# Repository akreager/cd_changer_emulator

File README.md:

# CD Changer Emulator

**Raspberry Pi-based CD changer emulator for vintage Kenwood car stereos**

Reverse-engineering the proprietary serial protocol used by 1990s Kenwood head units to communicate with their CD changers, and building an open-source emulator that replaces the changer with a Raspberry Pi — enabling unlimited music playback through the original stereo using its factory controls.

## Project Status

🔬 **Phase: Protocol Reverse Engineering** — Capturing and decoding the synchronous serial protocol between a Kenwood KRC-3006 cassette receiver and a KDC-C717 10-disc CD changer.

### Current Milestone

**Phase 1 of TP-KRC3006-01 — power-on characterization — was executed; closeout is pending.** Executed 2026-04-19 on the KRC-3006 with a KDC-C717 changer connected through the pass-through breakout board. The overall result, continuity P/F and several dispositions remain blank (DC-02); results are published in [TL-KRC3006-01-P1-20260419](./docs/records/TL-KRC3006-01-P1-20260419.pdf).

Findings that matter for the emulator design:

- **CH-CON (Pin 4) measures active-HIGH** — the line rises when the changer source is selected. This *conflicts* with the KDC-CX85 service manual, which documents it as active-LOW. To be re-confirmed against decoded traffic in Phase 2.
- **Pin 2 (GND) and Pin 6 (D.GND) show continuity** inside the head unit, which settles the grounding strategy for the HAT.
- **CLK (Pin 13) is gated, not continuous** — 0 Hz at idle, 31.6 Hz during playback, briefly ~100 Hz on a track change before settling back. These are DMM frequency readings on a gated line, not bit-rate measurements; bit-level clock timing awaits logic analyzer capture in Phase 2A.
- **Pin 10 (CH-DATAC) idles near 5 V**, not the LOW state predicted by the schematic analysis. Unexplained — still open.
- **The KDC-C717 is functional** — displays E-01 with no magazine, then loads and plays on insertion.

Testing runs inline through the DN-KRC3006-04 pass-through breakout board, serial number 1, assembled and verified per TP-KRC3006-02:

The KDC-CX85 originally used as the reference changer was diagnosed with a dead or degraded laser diode and retired. All further testing uses the KDC-C717:

For reference, the 13-pin mini DIN changer connector pinout:

### Immediate To-Do

- [ ] **Close out Phase 1** — Complete the missing results, deviations and changer-present observation in the separate supplement required by [D-1](.agents/decisions.md). The original [Phase 1 record](docs/records/TL-KRC3006-01-P1-20260419.pdf) stays unchanged; Phase 2A requires its overall disposition (DC-02/03).
- [ ] **Execute Phase 2A** — With the C717 connected and no magazine, capture the A/B/C power/source transitions, measure timing and decode a repeatable frame using [TP-01 §4.2](docs/TP-KRC3006-01.md#42-phase-2a-idle-capture-changer-connected-no-magazine) and the matching TL-01 tab. The head unit needs a changer present to select CD-CH; the supplement will record the date and setup of that owner observation.
- [ ] **Build and verify FIX-01 in parallel** — Modify breakout S/N 2 under [DN-04 §16](docs/DN-KRC3006-04.md#16-fix-01--clk-driver-fixture-breakout-sn-2); preserve S/N 1 for ordinary captures. These are approved build instructions, not a completed fixture record.
- [ ] **Execute Phase 2B** — Capture loaded C717 traffic, power-on/RESET behavior and possible protocol time fields under TP-01 §4.3. Resolve the ignition timing-reference method (DC-28) before that measurement.
- [ ] **Execute Phase 2C after 2B passes and FIX-01 is verified** — Identify the CLK driver under TP-01 §4.4. This result gates the CLK level-shifter choice.
- [ ] **Execute Phase 3 after 2B passes** — Map head-unit controls to commands and responses under TP-01 §4.5. Phase 2C does not gate Phase 3 (approved [R-1.5](.agents/rulings/2026-10-16.md)).
- [ ] **Review and continue the emulator HAT design** — The committed schematic/PCB is an initial state, not a completeness-reviewed design. Resolve the shifter A/B and Pi 5 UART mapping questions (DC-26), review the power section and layout, and use capture evidence for the remaining protocol decisions. Firmware and software implementation have not started.

### Completed

- [x] **Schematic analysis documented** — [DN-02](docs/DN-KRC3006-02.md) distinguishes the head-unit series resistors from the R145/R146 pull-downs and marks superseded controller-supply recommendations. CLK idle level remains open: the pull-down topology does not establish the driven bus level, and the [Phase 1 record](docs/records/TL-KRC3006-01-P1-20260419.pdf) measured CLK HIGH. The first Phase 2A capture will provide the evidence for the architect's wording update (DC-09).
- [x] **Breakout board design** — KiCad layout with two 13-pin mini DIN connectors and 2.54mm pin headers (ground adjacent to each signal) using Kenwood signal names on silkscreen. (DN-KRC3006-04)
- [x] **Connector footprint verification** — 3D-printed mockup confirmed pin spacing before committing to fab.
- [x] **Breakout board ordered** — 3 boards, OSH Park standard fab.
- [X] **Breakout S/N 1 verification record published** — [TL-KRC3006-02-01-20260410](docs/records/TL-KRC3006-02-01-20260410.pdf) records assembly and electrical verification. The missing step 1.1 board-outline result still needs owner disposition (DC-13).
- [X] **Set up test bench** — Bench wiring, logic analyzer connections, and a custom staged power adapter with two toggle switches that simulate constant and ignition-switched power independently.
- [X] **Troubleshoot CX85** — Initial tests showed the CD changer laser diode is dirty or degraded (E-04, all discs unreadable). Unit deemed inoperable and retired. Further testing is carried out with a KDC-C717 CD changer. (DN-KRC3006-06)
- [X] **Executed Phase 1 of TP-KRC3006-01; closeout pending** — Power-on characterization with the KDC-C717 inline: supply and idle current draw, 13-pin DIN idle-voltage readings (audio pins 8 and 12 were not tested), CH-CON polarity, CLK gating behavior, and pin 2 ↔ pin 6 ground continuity. Record: TL-KRC3006-01-P1-20260419.

## What This Project Does

This project emulates a Kenwood CD changer on the 13-pin round DIN connector used by mid-1990s Kenwood head units. The emulator responds to all head unit commands (play, stop, next/previous track, disc selection, repeat, shuffle) and streams audio from a Raspberry Pi through the stereo's built-in amplifier.

### Features (Planned)

- **Full protocol emulation** — Head unit displays disc number and track number.
- **10 virtual disc slots** — Map playlists to CD1–CD0, just like a real magazine. "Magazine overflow" (a playlist of playlists) allows more than ten playlists per magazine, wrapping to the next bank automatically when disc 10 finishes.
- **Web-based library management** — Build playlists and load virtual magazines from your phone over WiFi. FLAC-only library. By design there are **no playback controls in the web UI** — every transport command comes from the head unit, the same as a real changer. (DN-KRC3006-05)
- **Automotive power management** — Supercapacitor-backed graceful shutdown, cranking ride-through, battery monitoring.
- **WiFi standby mode** — When parked at home, the Pi stays on and connects to your home network for easy music transfers and system updates.
- **Custom Raspberry Pi HAT** — Single PCB with ATtiny1616 protocol controller, PCM5102A I2S DAC, automotive power supply, designed for JLCPCB or similar assembly.

## Target Hardware

| Component | Role |
|-----------|------|
| Kenwood KRC-3006 (or similar mid-90s Kenwood head unit) | The stereo — device under test |
| Kenwood KDC-C717 | CD auto changer — reference changer for protocol capture |
| Raspberry Pi 5 | Media server, web interface, audio playback |
| ATtiny1616 | Real-time Kenwood protocol handler (on custom HAT), run at 3.3V to match Pi GPIO natively |
| SN74LVC8T245PWR ×2 | 3.3V ↔ 5V bus level shifting, one per direction |
| PCM5102A I2S DAC | Digital-to-analog audio conversion |
| 1 TB NVMe SSD | Music storage (avoids SD card corruption) |
| SparkFun TOL-18627 USB Logic Analyzer | Protocol capture and analysis |
| Custom staged power adapter | Two toggle switches simulating constant and ignition power independently on the bench |

## Target Vehicle

Any vintage automobile still using a Kenwood head unit with CD changer control. I am building this and testing around a KRC-3006 head unit due to it being the only shaft style cassette deck with a CD changer control port. My vehicle for this project is a 1985 Chevrolet C10 Silverado. The power supply design accounts for the electrically noisy environment of older vehicles without modern filtering.

## Repository Structure

This overview shows tracked project files and directories. Entries marked `(planned)` have no tracked files and will not appear in a fresh clone. The legacy software directory names are retained from the original plan; [DN-KRC3006-05](./docs/DN-KRC3006-05.md) describes the current software architecture.

```
cd_changer_emulator/
├── AGENTS.md                # Instructions for AI agents working on this repo
├── CLAUDE.md                # Imports the shared agent instructions
├── .agents/                 # Agent workspace: rules, context, decisions, handoffs, backlogs, skills
├── assets/                  # Project assets. Photos and screenshots.
├── docs/                    # Project documentation
│   ├── TP-KRC3006-01.md     # Test plan 1: Protocol capture test procedure (IEEE 829)
│   ├── TL-KRC3006-01.fods   # Test log 1: Companion log workbook to TP-KRC3006-01 (flat ODF)
│   ├── TP-KRC3006-02.md     # Test plan 2: Breakout board test plan
│   ├── TL-KRC3006-02.fodt    # Test log 2: Breakout board test log
│   ├── TP-KRC3006-03.md     # Test plan 3: Emulator test procedure (IEEE 829)
│   ├── TL-KRC3006-03.fods    # Test log 3: Companion log workbook to TP-KRC3006-03
│   ├── DN-KRC3006-01.md     # Design note 1: HAT design research
│   ├── DN-KRC3006-02.md     # Design note 2: Schematic analysis
│   ├── DN-KRC3006-03.md     # Design note 3: Bluetooth stretch goal
│   ├── DN-KRC3006-04.md     # Design note 4: Breakout board design
│   ├── DN-KRC3006-05.md     # Design note 5: Web application design for library management
│   ├── DN-KRC3006-06.md     # Design note 6: Kenwood CD changer error codes
│   ├── protocol/            # Protocol workspace; currently README only
│   └── records/             # Published test records; see docs/README.md
├── firmware/                # Firmware workspace
│   ├── README.md            # Existing firmware documentation
│   └── src/                 # (planned) Firmware source
├── software/                # Raspberry Pi software workspace
│   ├── README.md            # Existing software documentation
│   ├── flask-app/           # (planned) Web interface; legacy directory name
│   ├── mpd-config/          # (planned) Playback configuration; legacy directory name
│   ├── power-mgmt/          # (planned) ATtiny UART bridge and power state management
│   └── wifi-manager/        # (planned) AP/client mode switching
├── hardware/                # KiCad PCB design files
│   ├── kicad/
│   │   ├── changer cable breakout/  # Pass-through breakout board (complete, fabbed)
│   │   ├── emulator hat/            # Raspberry Pi HAT (schematic in progress)
│   │   └── lib/                     # Shared custom symbols and footprints
│   ├── gerbers/             # (planned) Manufacturing files
│   └── bom/                 # (planned) Bill of materials with JLCPCB part numbers
├── captures/                # Capture workspace; currently README only
├── diagrams/                # Diagram workspace; currently README only
└── reference/               # Citation register with external links
```

## Kenwood Compatibility

This project targets the **"O protocol"** (Old protocol) used by Kenwood head units with the round 13-pin DIN CD changer connector, roughly 1990–1998. Known compatible head units include models in the KRC series (cassette receivers) and some KDC series (CD receivers) from that era [citation needed].

Later Kenwood units with a rectangular changer connector use the "C protocol" (New protocol), which has different command encoding. This project does not currently target the C protocol, but the hardware and architecture could be adapted [citation needed].

## Documentation

The project follows a documentation-first approach using IEEE 829-inspired test procedures. All documentation lives in the `docs/` directory. Test plans and design notes are written in Markdown and render directly on GitHub. Test logs are bench forms edited in LibreOffice: TL-01 and TL-03 use flat ODF spreadsheets (`.fods`); TL-02 uses flat ODF text (`.fodt`), per D-10.

Test plans and test logs are created and maintained as matched pairs sharing a sequence number — `TP-KRC3006-01` defines what gets tested and how, and `TL-KRC3006-01` is where results are recorded. Filled-out copies of a log are published as PDF in `docs/records/` as each phase completes.

| Document Name | Type | Description |
|----|------|-------------|
| [TP-KRC3006-01](./docs/TP-KRC3006-01.md) | Test Plan | Rev D draft: D-2/D-3 metadata; inline captures, CLK driver identification and command mapping |
| [TL-KRC3006-01](./docs/TL-KRC3006-01.fods) | Test Log | Rev D draft: document-control header; historical Phase 1 results retained |
| [TP-KRC3006-02](./docs/TP-KRC3006-02.md) | Test Plan | Breakout board test plan |
| [TL-KRC3006-02](./docs/TL-KRC3006-02.fodt) | Test Log | Breakout board test log |
| [TP-KRC3006-03](./docs/TP-KRC3006-03.md) | Test Plan | Test plan for creating and testing protocol emulation through full audio integration |
| [TL-KRC3006-03](./docs/TL-KRC3006-03.fods) | Test Log | Flat-ODF log with conditional time-field and UART rate-selection tables |
| [DN-KRC3006-01](./docs/DN-KRC3006-01.md) | Design Note | HAT design research — ATtiny1616 selection, PCM5102A DAC circuit, automotive power supply with supercap, WiFi architecture, JLCPCB assembly |
| [DN-KRC3006-02](./docs/DN-KRC3006-02.md) | Design Note | Schematic analysis — KRC-3006 head unit and KDC-CX85 changer signal routing, series resistor values, protocol variant identification |
| [DN-KRC3006-03](./docs/DN-KRC3006-03.md) | Design Note | Bluetooth stretch goal — wireless audio streaming while retaining factory head unit controls |
| [DN-KRC3006-04](./docs/DN-KRC3006-04.md) | Design Note | Breakout board design — pass-through 13-pin mini DIN breakout with logic analyzer headers |
| [DN-KRC3006-05](./docs/DN-KRC3006-05.md) | Design Note | Web Application Design for Emulator Library Management |
| [DN-KRC3006-06](./docs/DN-KRC3006-06.md) | Design Note | Kenwood CD Changer Error Codes |

Per-document revision status is tracked in the [documentation index](./docs/README.md).

### Completed Test Records

| Record | Covers | Date |
|----|------|------|
| [TL-KRC3006-01-P1-20260419](./docs/records/TL-KRC3006-01-P1-20260419.pdf) | TP-KRC3006-01 Phase 1 — power-on characterization | 2026-04-19 |
| [TL-KRC3006-02-01-20260410](./docs/records/TL-KRC3006-02-01-20260410.pdf) | TP-KRC3006-02 — breakout board serial number 1 | 2026-04-10 |

## Building / Contributing

This project is in early development. If you have a compatible Kenwood head unit and want to help with protocol capture, testing, or firmware development, contributions are welcome.

If you use an AI coding agent on this repo, point it at [AGENTS.md](AGENTS.md) first.

### Prerequisites

- [Arduino IDE](https://www.arduino.cc/en/software) with [megaTinyCore](https://github.com/SpenceKonde/megaTinyCore) installed
- [PulseView](https://sigrok.org/wiki/PulseView) for logic analyzer captures
- [KiCad](https://www.kicad.org/) for PCB design
- Python 3 with [FastAPI](https://fastapi.tiangolo.com/) for the web interface and [python-mpv](https://github.com/jaseg/python-mpv) for playback
- [LibreOffice](https://www.libreoffice.org/) to open the flat ODF test logs (`.fodt` and `.fods`)
- A UPDI programmer for the ATtiny1616 ([Adafruit UPDI Friend](https://www.adafruit.com/product/5879) or DIY with a serial adapter and resistor)

## References

- [Mictronics CDC Protocol Documentation](https://www.mictronics.de/) (Kenwood command tables)
- [Elektroda.pl Kenwood Slim CD Changer Emulator](https://www.elektroda.pl/rtvforum/topic536235.html) (szymtro's 8051 implementation)
- [AVRFreaks: Kenwood CD Changer → Serial Strings](https://www.avrfreaks.net/forum/kenwood-cd-changer-serial-strings)
- [Pinouts.ru: Kenwood 13-pin DIN connector](https://old.pinouts.ru/CarAudio/kenwood_cd_changer_pinout.shtml)
- [SpenceKonde/megaTinyCore](https://github.com/SpenceKonde/megaTinyCore) (ATtiny1616 Arduino support)
- [pyupdi / pymcuprog](https://github.com/mraardvark/pyupdi) (UPDI programming from Raspberry Pi)

- [KRC-3006 Owner's Manual](https://archive.org/details/manualzilla-id-6478282/mode/2up?q=kenwood+%22krc-3006%22) (REF-001)
- [KDC-CX85/CPS85 Service Manual](https://www.manualslib.com/manual/836703/Kenwood-Kdc-Cx85.html) (REF-005; historical changer)
- [SparkFun TOL-18627 analyzer specifications](https://www.sparkfun.com/usb-logic-analyzer-24mhz-8-channel.html) (REF-006)
- [KDC-C517FM / KDC-C717/Y Service Manual](https://www.manualslib.com/manual/850190/Kenwood-Kdc-C517fm.html) (REF-007)
- [KDC-C717 Instruction Manual](https://www.manualslib.com/manual/896906/Kenwood-Kdc-C717.html) (REF-008; project-copy edition match pending)
- [Full citation register](reference/README.md), including the KRC-3006 service manual's pending public source (REF-004).

## License

This project is licensed under the [MIT License](LICENSE) — you're free to use, modify, and distribute this project for any purpose, including commercial use.

## Revision History

Legacy rows retain their original revision labels, dates and attributions. “Not recorded” identifies missing drafting-model/date or approval/date evidence; it is not a retrospective sign-off. New entries follow D-2/D-3.

| Rev | Date | Legacy attribution | Drafted / date | Approved / date | Changes |
|---|---|---|---|---|---|
| — | 2026-10-15 | A. Kreager | Not recorded | Not recorded | DC-11: distinguish tracked content from planned directories in the repository tree. |
| — | 2026-10-17 | A. Kreager | Not recorded | Not recorded | CP-1: link TP-01 in Markdown and update format notes per D-9/D-10; plan content unchanged. |
| — | 2026-10-17 | A. Kreager | Not recorded | Not recorded | CP-1: link TP-03 in Markdown; plan content unchanged. |
| — | 2026-10-17 | A. Kreager | Not recorded | Not recorded | CP-1: link TP-02 in Markdown and complete the format and prerequisite updates; plan content unchanged. |
| — | 2026-10-17 | A. Kreager | Not recorded | Not recorded | TP-01/TL-01 Rev C per rulings R-1; update capture work order and Phase 1 closeout status. |
| — | 2026-10-17 | A. Kreager | Not recorded | Not recorded | D-10: convert TL-03 to flat ODF; R-5/R-6: align emulator plan/log criteria and UART rate selection. |
| — | 2026-10-17 | A. Kreager | Not recorded | Not recorded | DC-14: synchronize SparkFun and factory-manual links with the reference register. |
| — | 2026-10-17 | A. Kreager | Not recorded | Not recorded | D-10/DC-16: convert TL-02 to flat ODF and add DN-06 revision history without changing technical content. |
| — | 2026-10-17 | A. Kreager | Not recorded | Not recorded | R-1.1: add SparkFun analyzer specification source (REF-006). |
| — | 2026-10-17 | — | Codex GPT-6 2026-10-17 | A. Kreager — pending | DC-29: align status and work order with R-1; keep Phase 1 and TL-02 gaps visible; distinguish committed HAT design from reviewed completeness. |
| - | 2026-10-17 | — | Codex GPT-6 2026-10-17 | A. Kreager — pending | DC-16/17: synchronize TP/TL-01 metadata revision and distinguish drafts from execution progress. D-2/D-3 applies to controlled-document headers. |

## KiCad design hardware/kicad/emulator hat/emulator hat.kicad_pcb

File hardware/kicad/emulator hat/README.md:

# Kenwood CD Changer Emulator HAT

KiCad project for a Raspberry Pi 5 HAT that emulates a Kenwood CD changer over the proprietary "O protocol" bus. Designed for the KRC-3006 shaft-style cassette head unit, replacing a 10-disc changer with unlimited FLAC playback controlled entirely from the factory head unit.

## Current Status

**Early schematic layout.** The protocol and audio front end is placed — ATtiny1616, two SN74LVC8T245 level shifters, PCM5102A DAC, 40-pin Pi header, and the 13-pin mini DIN changer port — along with supporting passives based on the PCM5102A reference design. The automotive power supply section has not been drawn yet, and no PCB layout work has begun.

Protocol reverse engineering via the breakout board (DN-KRC3006-04) is the active priority. Full command mapping must be complete before the HAT schematic can be finalized.

## Design Overview

The HAT consolidates four subsystems onto a single board:

- **ATtiny1616 protocol controller** — Handles all real-time Kenwood bus communication at 3.3V, translated to 5V bus levels via two SN74LVC8T245PWR level shifters. Communicates with the Pi over a dedicated UART.
- **PCM5102A I2S DAC** — Converts digital audio from the Pi to analog line-level output for the head unit's CD changer input.
- **Automotive power supply** — Accepts 12V from the head unit (constant B.U. and ignition-switched), regulates to 5V/3.3V with power sequencing and soft-shutdown support.
- **Connectors and interface** — 13-pin mini DIN bus connection, UPDI programming header (dedicated UART3 on GPIO4/5), status LEDs, test points.

Every bus signal will carry a 100 Ω inline series resistor, matching the protection scheme the KDC-CX85 uses on its own connector. Per DN-KRC3006-02 Rev C the bus is a conventional fast 5V TTL/CMOS bus — the head unit's own series resistors range from 100 Ω to 7.5 KΩ and the 100K parts on DATA H and CLK are pull-downs to ground that define the idle-LOW state, not series elements. No edge-rate compensation or Schmitt-trigger conditioning is needed.

All music logic — playlist management, FLAC decoding, library browsing — runs on the Raspberry Pi via python-mpv. The ATtiny handles only the protocol state machine and handshake timing.

## Settled by Phase 1 Testing

TP-KRC3006-01 Phase 1 (power-on characterization, 2026-04-19) resolved two questions that affect this board:

- **Audio ground topology** — Pins 2 (GND) and 6 (D.GND) measured continuous inside the head unit. They can be treated as a single ground on the HAT.
- **CH-CON (Pin 4) polarity** — Measured active-HIGH: the line rises when the changer source is selected. This conflicts with the KDC-CX85 service manual, which documents it as active-LOW, so it will be re-confirmed against decoded traffic in Phase 2 before the input stage is committed.

Phase 1 also found Pin 10 (CH-DATAC) idling near 5 V rather than the LOW state the schematic analysis predicted. That is still unexplained and may affect how the HAT drives or reads that line.

## Open Constraints

Several items still depend on data from the ongoing reverse engineering effort (TP-KRC3006-01):

- **CLK signal directionality** — The CX85 service manual lists CLK as I/O on the changer side. If Phase 2C confirms it is bidirectional, the CLK channel must use an SN74LVC1T45 (independent DIR pin) instead of the fixed-direction 74LVC8T245.
- **Power sequencing** — The ATtiny must be ready to respond before the Pi finishes booting (~20s). Autonomous status responses during early boot may be required.
- **DAC output level matching** — Analog output must match the stock changer's level to avoid volume discontinuity. To be verified during integration testing.

## Related Documentation

| Document | Description |
|----------|-------------|
| DN-KRC3006-01 | HAT design research — component selection, pin mapping, architecture |
| DN-KRC3006-02 | KRC-3006 and KDC-CX85 schematic analysis — bus impedance, signal conditioning |
| DN-KRC3006-04 | 13-pin mini DIN breakout board (complete, used for protocol capture) |
| TP-KRC3006-01 | Reverse engineering plan: Phase 1 executed, closeout pending; inline Phase 2A next; Phase 2C identifies CLK driver |
| TP-KRC3006-03 | Emulator development and integration test plan (waiting for TP-01) |

## License

MIT — see repository root.

## Revision History

| Rev | Date | Legacy attribution | Drafted / date | Approved / date | Changes |
|---|---|---|---|---|---|
| — | 2026-10-17 | A. Kreager | Not recorded | Not recorded | Align test-plan revision and CLK direction gate with approved R-1.5/R-1.6. Existing hardware summary remains unverified against initial-state commit 96d09e0; CLK idle wording awaits Phase 2A. |
| - | 2026-10-17 | — | Codex GPT-6 2026-10-17 | A. Kreager — pending | Synchronize current document references after D-2/D-3 metadata revisions. Historical Rev C analysis and unresolved CLK idle claim remain for DC-09. |

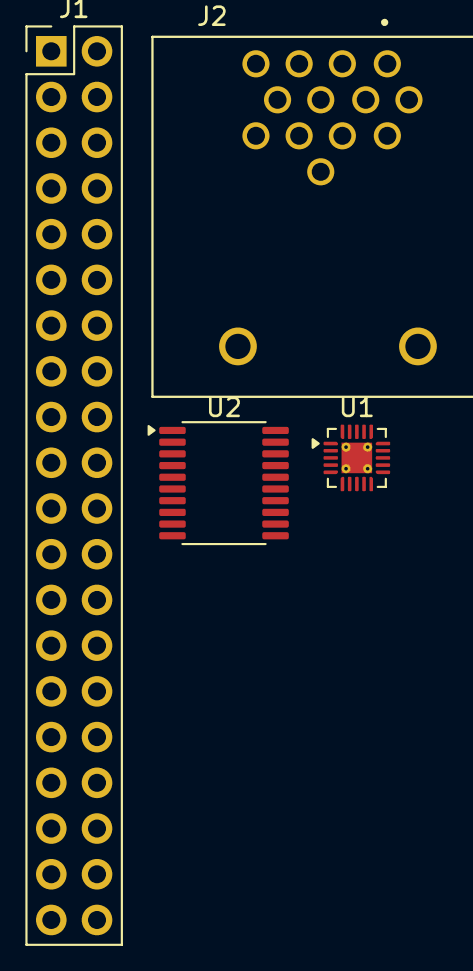
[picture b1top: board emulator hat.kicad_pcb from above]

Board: 2 copper layers, 4 parts (0 on the bottom side), 4 nets, no tracks yet.

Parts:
J1: Raspberry_Pi_2_3; PinHeader_2x20_P2.54mm_Vertical
J2: SDD-130J; CUI_SDD-130J
U1: ATtiny1616-M; VQFN-20-1EP_3x3mm_P0.4mm_EP1.7x1.7mm_ThermalVias
U2: PCM5102A; TSSOP-20_4.4x6.5mm_P0.65mm

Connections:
unnamed: J1.1 (3V3), J1.17 (3V3)
unnamed: J1.2 (5V), J1.4 (5V)
unnamed: J1.6 (GND), J1.9 (GND), J1.14 (GND), J1.20 (GND), J1.25 (GND), J1.30 (GND), J1.34 (GND), J1.39 (GND)
unnamed: U1.3 (GND), U1.21 (GND)

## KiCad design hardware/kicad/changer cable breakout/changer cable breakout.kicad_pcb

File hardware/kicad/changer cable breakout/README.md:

# KRC-3006 Pass-Through Breakout Board (DN-KRC3006-04)

## Purpose

This KiCad project implements a passive, pass-through breakout board for the Kenwood KRC-3006 head unit's 13-pin mini DIN connector. The board provides:

- **Signal routing** between the KRC-3006 and connected CD autochanger.
- **Accessible test points** for bus signal analysis and protocol reverse engineering.
- **Isolated audio path** with independent head unit and changer TRS audio jack connectors.

## Current Status

**S/N 1 verification record published; closeout gap remains** — Boards received 2026-03-28 from OSH Park. S/N 1 verification completed 2026-04-10, per [TL-02-01-20260410](../../../docs/records/TL-KRC3006-02-01-20260410.pdf). Its step 1.1 result remains a closeout question (DC-13). Phase 1 of TP-01 used S/N 1; further capture entry depends on Phase 1 closeout under DC-02/03.

## Schematic Summary

| Ref Des | Component | Function |
|---|-------|-------|
| J1 | SDD-130J, 13-pin mini DIN female | Head unit side connector (front side) |
| J2 | SDD-130J, 13-pin mini DIN female | Changer side connector (back side) |
| J3 | 1×11 female pin header, 2.54 mm pitch | Digital/control signal test points |
| J4 | STX-3100-3NB, 3.5 mm TRS audio jack | Head unit side audio breakout |
| J5 | STX-3100-3NB, 3.5 mm TRS audio jack | Changer side audio breakout |

## J1/J2 Pinout

| Pin | Signal | Description |
|-----|--------|-----------|
| 1 | REQ H (Active Low)  | Request handshake output from head unit. |
| 2 | GND | Ground (factory name; DN-02 §1). |
| 3 | B.U.  | Battery Unswitched. |
| 4 | ON  | Changer connect/enable signal. |
| 5 | MUTE  | Mute request line. |
| 6 | D. GND | Digital ground. |
| 7 | RESET  | Reset pulse output to changer. |
| 8 | R CH  | Right audio channel, analog. |
| 9 | REQ C (Active Low)  | Request handshake output from changer to head unit. |
| 10 | DATA C  | Serial data from changer to head unit. |
| 11 | DATA H  | Serial data from head unit to changer. |
| 12 | L CH  | Left audio channel, analog. |
| 13 | CLK (Active Low)  | Synchronous clock. |

## J3 Pinout

|  J3 Pin  |  J1 Pin  |  Signal  |
| --- | --- | --- |
| 1 | 2 |  GND  |
| 2 | 4 |  ON (CH-CON)  |
| 3 | 3 |  B.U. (+14V)  |
| 4 | 7 |  RESET  |
| 5 | 6 |  D. GND  |
| 6 | 1 |  REQ H (Active Low)  |
| 7 | 9 |  REQ C (Active Low)  |
| 8 | 5 |  MUTE  |
| 9 | 10 |  DATA C  |
| 10 | 11 |  DATA H  |
| 11 | 13 |  CLK (Active Low)  |

## J4 Pinout

| J4 contact | J1 pin | Signal |
|---|---|---|
| Tip | 8 | R ch (to head unit) |
| Ring | 12 | L ch (to head unit) |
| Sleeve | 2 | GND |

## J5 Pinout

| J5 contact | J2 pin | Signal |
|---|---|---|
| Tip | 8 | R ch (from changer) |
| Ring | 12 | L ch (from changer) |
| Sleeve | 2 | GND |

These are contact labels, not numbered pins. Mapping follows approved [R-4](../../../.agents/rulings/2026-10-16.md), which cites the PCB and TL-02 steps 1.12–1.13 and 3.3–3.4. This corrects the README labels only.

## Audio Interception

The audio channels (Pin 8 - R CH and Pin 12  L CH) are not routed as a direct pass-through between J1 and J2. Instead, they are broken out to two 3.5 mm TRS audio jacks mounted on the right edge of the board:

- **J4** — Head unit side audio. Tip = R CH, Ring = L CH, Sleeve = GND.
- **J5** — Changer side audio. Tip = R CH, Ring = L CH, Sleeve = GND.

The audio jacks use a standard 3-conductor (TRS) footprint with no switching contacts. When nothing is plugged in, the audio pins on both the head unit and changer sides float.

This topology enables three operating modes:

| Mode | Configuration | Use Case |
|---|---|---|
| **Audio pass-through** | Connect J4 to J5 with a male-to-male 3.5 mm TRS cable. | Normal protocol capture with authentic changer audio reaching the head unit. |
| **Audio intercept** | Connect monitoring equipment (oscilloscope, audio recorder, powered speakers) to J5. | Listen to or record the changer's audio output without routing it to the head unit. |
| **Audio injection** | Connect an external audio source to J4. Leave J5 disconnected or connected to monitoring equipment. | Feed test tones or music from a phone, DAC, or Raspberry Pi directly into the head unit's audio input path. Useful for verifying the audio path independently of changer protocol state. |

Audio pass-through requires the external cable. The board cannot function as a fully transparent sniffer without it. This is an intentional design decision — the separate jacks provide flexibility that a hardwired pass-through cannot.

## Next Steps

S/N 1 supported TP-01 Phase 1 on 2026-04-19. After the current [TP-01](../../../docs/TP-KRC3006-01.md) and TL-01 revisions are approved and Phase 1 is dispositioned:

1. Phase 2A: inline capture with the C717 connected and no magazine, after Phase 1 closeout.
2. Phase 2B: loaded-changer initialization, steady playback, power-on and time-field captures.
3. Build FIX-01 in parallel with the earlier capture work; execute Phase 2C after Phase 2B passes: CLK driver identification with **FIX-01, modified S/N 2**, built and verified per [DN-04 §16](../../../docs/DN-KRC3006-04.md#16-fix-01--clk-driver-fixture-breakout-sn-2). Keep S/N 1 unmodified.
4. Phase 3: command mapping after Phase 2B passes; Phase 2C is not its entry gate (R-1.5). TP-03 emulator development and integration follows TP-01 completion.

For every analyzer connection follow DN-04 §7: power down, block J3-3, ground only at J3-1, leave J3-5 empty, use the custom crimped harness and cover exposed rear joints (R-2).

## References

- Service manual: Kenwood KRC-3006 Cassette Head Unit
- Service manual: Kenwood KDC-C717 CD Changer
- Related design docs: DN-KRC3006-02 (Schematic Analysis), DN-KRC3006-04

## Revision History

| Rev | Date | Legacy attribution | Drafted / date | Approved / date | Changes |
|---|---|---|---|---|---|
| — | 2026-10-17 | A. Kreager | Not recorded | Not recorded | R-4: correct J4/J5 contact and channel labels. DC-05/13: factory ground name, recorded completion date and TP-01 Rev C work order; link FIX-01 instructions. |
| - | 2026-10-17 | — | Codex GPT-6 2026-10-17 | A. Kreager — pending | DC-13: distinguish the published S/N 1 verification from the missing step 1.1 disposition; synchronize current-plan references and FIX-01 sequencing with the root README. |

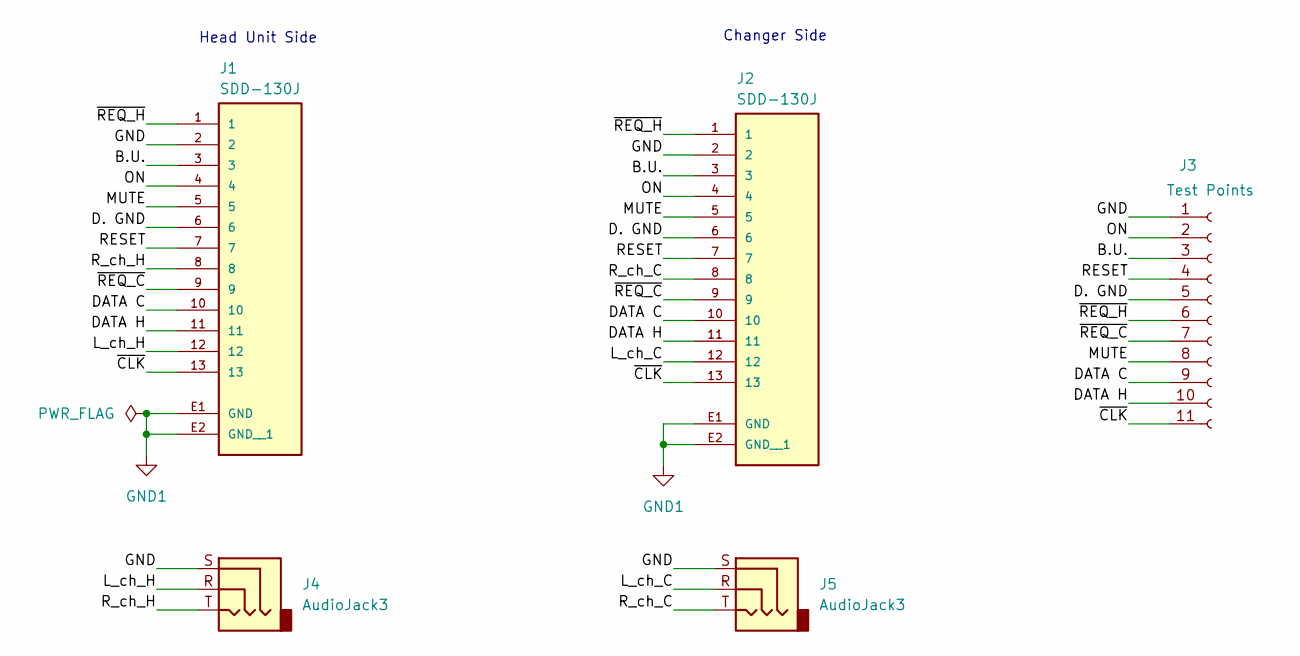
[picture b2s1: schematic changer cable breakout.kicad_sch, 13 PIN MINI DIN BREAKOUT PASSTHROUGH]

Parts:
J1, J2: SDD-130J; CUI_SDD-130J; PARTREV 1.06/02-13-2020
J3: Test Points; PinSocket_1x11_P2.54mm_Vertical
J4, J5: AudioJack3; Jack_3.5mm_CUI_SJ1-3523N_Horizontal

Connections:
/B.U.: J1.3, J2.3, J3.3
/D. GND: J1.6, J2.6, J3.5
/DATA C: J1.10, J2.10, J3.9
/DATA H: J1.11, J2.11, J3.10
/GND: J1.2, J2.2, J3.1, J4.S, J5.S
/L_ch_C: J2.12, J5.R
/L_ch_H: J1.12, J4.R
/MUTE: J1.5, J2.5, J3.8
/ON: J1.4, J2.4, J3.2
/RESET: J1.7, J2.7, J3.4
/R_ch_C: J2.8, J5.T
/R_ch_H: J1.8, J4.T
/~CLK: J1.13, J2.13, J3.11
/~REQ_C: J1.9, J2.9, J3.7
/~REQ_H: J1.1, J2.1, J3.6
GND1: J1.E1 (GND), J1.E2 (GND__1), J2.E1 (GND), J2.E2 (GND__1)

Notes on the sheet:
Head Unit Side
Changer Side

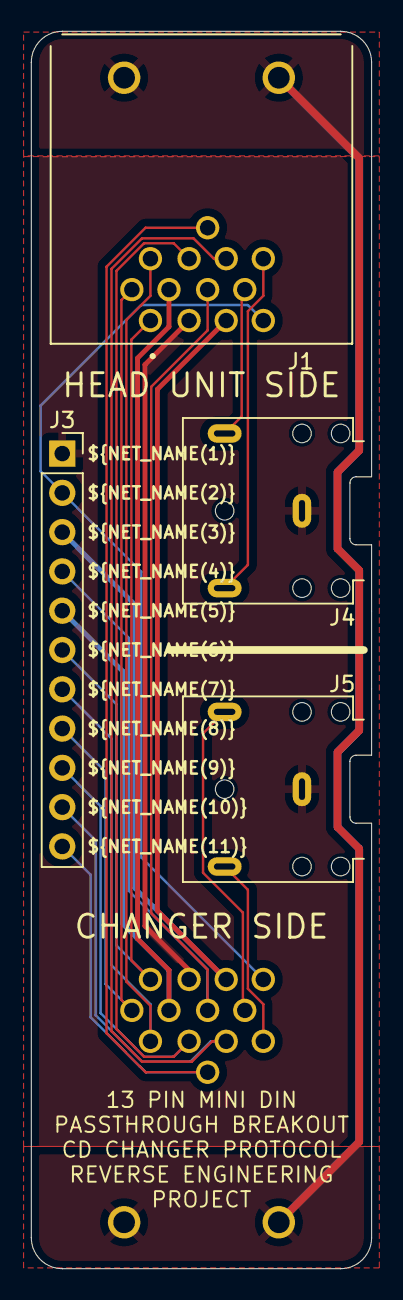
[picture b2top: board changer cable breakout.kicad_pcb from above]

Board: 2 copper layers, 22.0 x 80.0 mm, 5 parts (1 on the bottom side), 16 nets.

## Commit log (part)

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2026-03-08 Create project file structure.
2026-03-08 add reference docs
    Add service manuals for KRC-3006 and KDC-CX85. Add schematics for KRC-3006. Add KRC-3006 owners manual.
2026-03-08 Add documents
2026-03-08 Update README.md
    change to open document formats
2026-03-09 Start KiCAD project
2026-03-09 Update and rename DR-KRC3006-002-HAT-Design-Research.md to DN-KRC3006-01.md
    changed document to align with new naming scheme.
2026-03-10 Add 13pin mini DIN connector datasheet
2026-03-10 rename and update test plan and test log docs.
2026-03-10 remove commercial datasheets and service manuals
2026-03-10 Add DN-KRC3006-04 to README.md
2026-03-10 start symbol and footprint library for project
2026-03-10 move emulator hat to subfolder
2026-03-10 start cable breakout design
2026-03-11 add 3d model
2026-03-11 make schematic and start layout
2026-03-12 Update DN-KRC3006-04.md
    Revision B. See Section 11 Revision History.
2026-03-14 update footprints
2026-03-14 finish breakout design
2026-03-15 Finalize breakout design
2026-03-15 Update DN-KRC3006-04.md
    Rev C Final
2026-03-15 Add test plan and test log for breakout board
2026-03-16 Update README.md
    Add relative links to documentation.
2026-03-21 Update .gitignore
    hide kicad 10 .history
2026-03-21 Update DN-KRC3006-01.md
    updated for decision to run attiny1616 at 3.3v and add level shifters for changer bus.
2026-03-21 Create design-block-lib-table
2026-03-21 Update DN-KRC3006-01.md
    update for decision to use separate uarts for communication and updi programming from pi to attiny.
2026-03-21 Update DN-KRC3006-02.md
    rev c with correct bus impedance.
2026-03-22 Update README.md
    Corrected bus impedance.
2026-03-29 update test plan 2
    rev b see document for changes
2026-03-29 Create README.md
    add document records folder
2026-04-11 update board assembly test plan and test log
    rev b
2026-04-11 complete board serial number 1
2026-04-13 Update test plan 01
    Rev B
2026-04-13 Create Test plan 3
    4 phases of protocol emulation creation
2026-04-13 test bench photo dump
2026-04-19 update assets
2026-04-20 Create TL-KRC3006-01-P1-20260419.pdf
    phase 1 completed.
